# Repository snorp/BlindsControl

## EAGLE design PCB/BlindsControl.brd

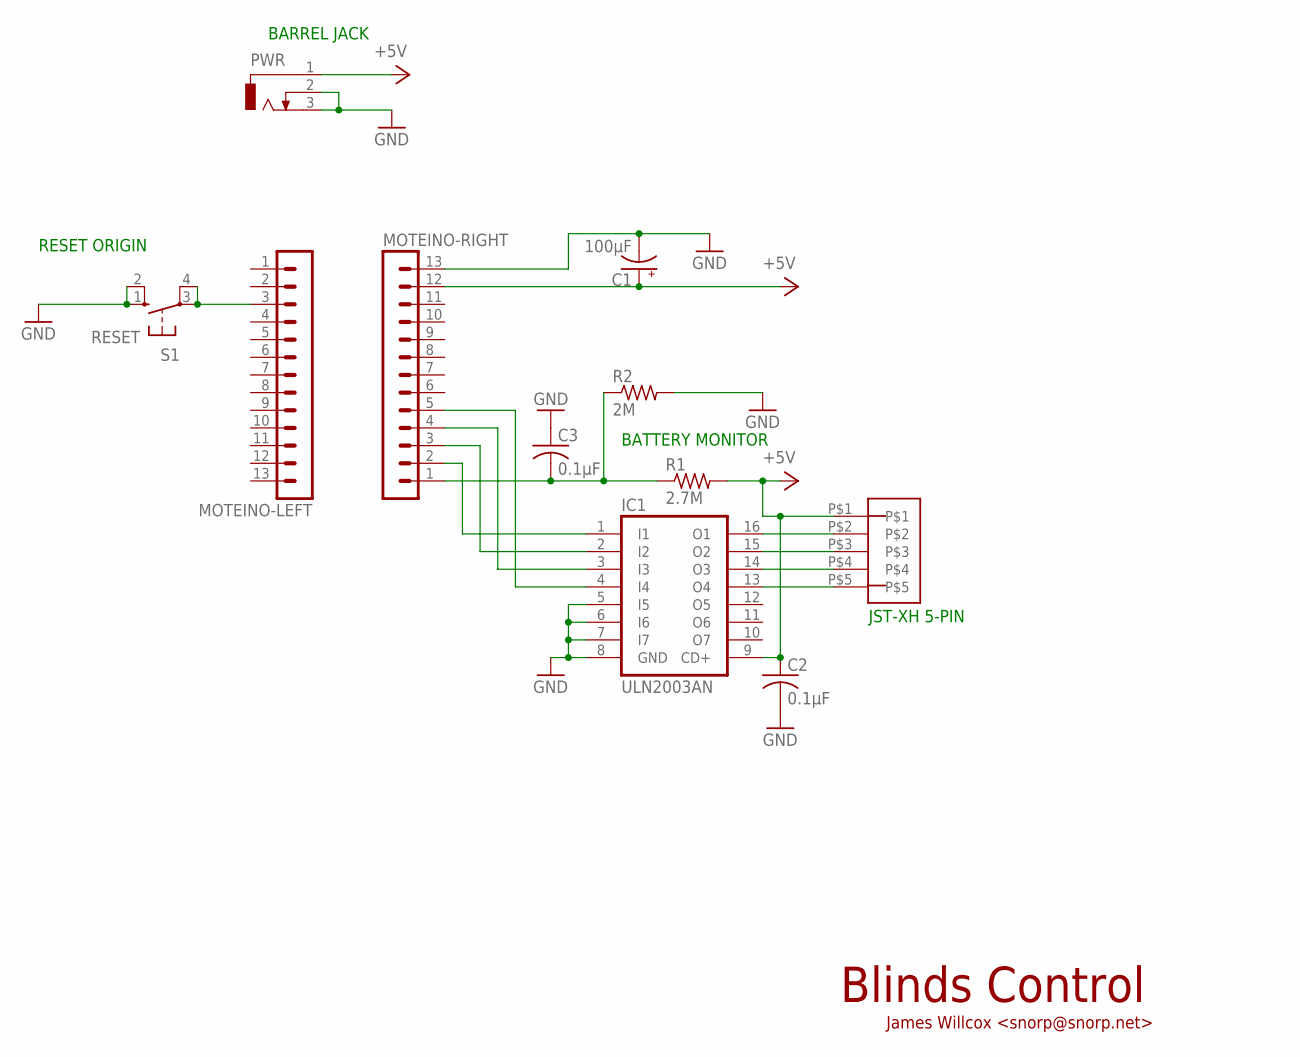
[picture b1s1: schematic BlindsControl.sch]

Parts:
C1: 100µF; TAP5-60
C2, C3: 0.1µF; C025-025X050
IC1: ULN2003AN; DIL16
MOTEINO-LEFT: MA13-1
MOTEINO-RIGHT: MA13-1
PWR: DCJ0303
R1: 2.7M; 0207/7
R2: 2M; 0207/7
S1: RESET; B3F-10XX
U$1: 5_PIN_JST-XH

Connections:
+5V: C1.+, C2.1, IC1.9 (CD+), MOTEINO-RIGHT.12, PWR.1, R1.2, U$1.P$1
GND: C1.-, C2.2, C3.1, IC1.5 (I5), IC1.6 (I6), IC1.7 (I7), IC1.8 (GND), MOTEINO-RIGHT.13, PWR.2, PWR.3, R2.2, S1.1 (S), S1.2 (S1)
unnamed: C3.2, MOTEINO-RIGHT.1, R1.1, R2.1
unnamed: IC1.1 (I1), MOTEINO-RIGHT.2
unnamed: IC1.2 (I2), MOTEINO-RIGHT.3
unnamed: MOTEINO-LEFT.3, S1.3, S1.4 (P1)
unnamed: IC1.3 (I3), MOTEINO-RIGHT.4
unnamed: IC1.4 (I4), MOTEINO-RIGHT.5
unnamed: IC1.16 (O1), U$1.P$2
unnamed: IC1.15 (O2), U$1.P$3
unnamed: IC1.14 (O3), U$1.P$4
unnamed: IC1.13 (O4), U$1.P$5

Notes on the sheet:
BARREL JACK
BATTERY MONITOR
RESET ORIGIN
JST-XH 5-PIN
Blinds Control
James Willcox <snorp@snorp.net>

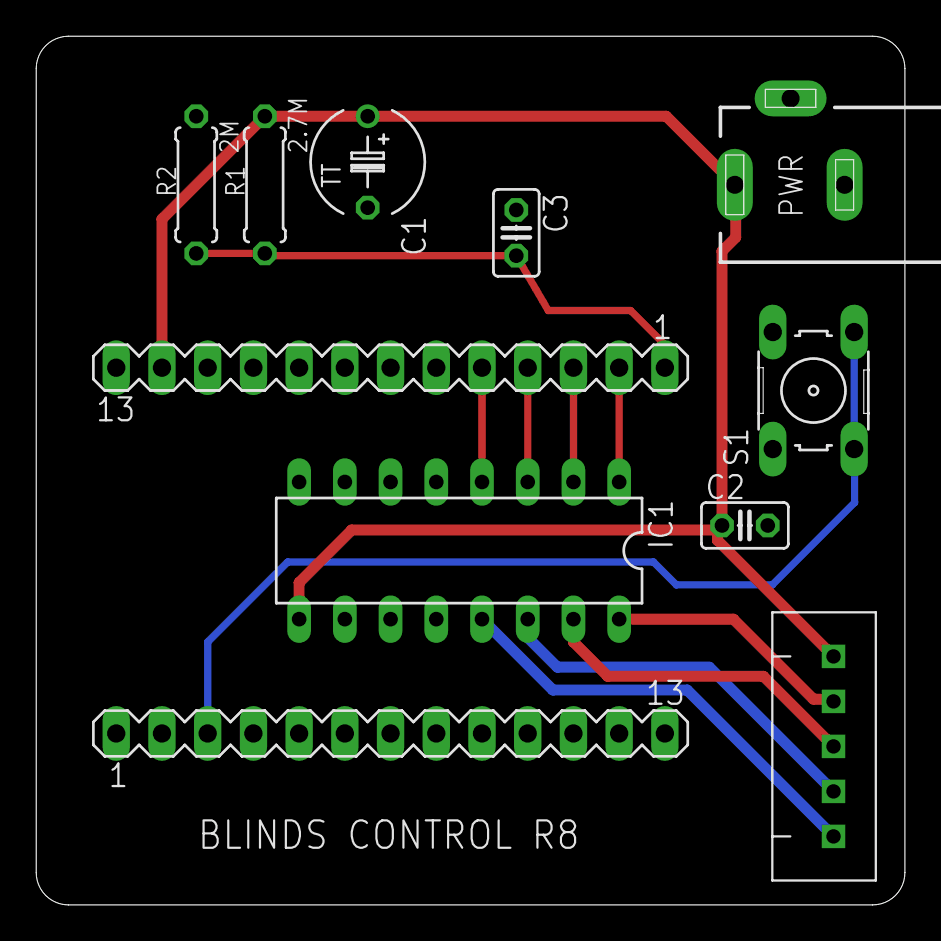
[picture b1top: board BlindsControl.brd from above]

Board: 2 copper layers, 48.3 x 48.3 mm, 11 parts (0 on the bottom side), 12 nets.

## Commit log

2016-08-25 Long-press on button resets to factory defaults
2016-09-23 Add 'release' and 'debug' environments
